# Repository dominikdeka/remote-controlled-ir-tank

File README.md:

# remote-controlled-ir-tank
Arduino based remote controlled vehicle with ir gun

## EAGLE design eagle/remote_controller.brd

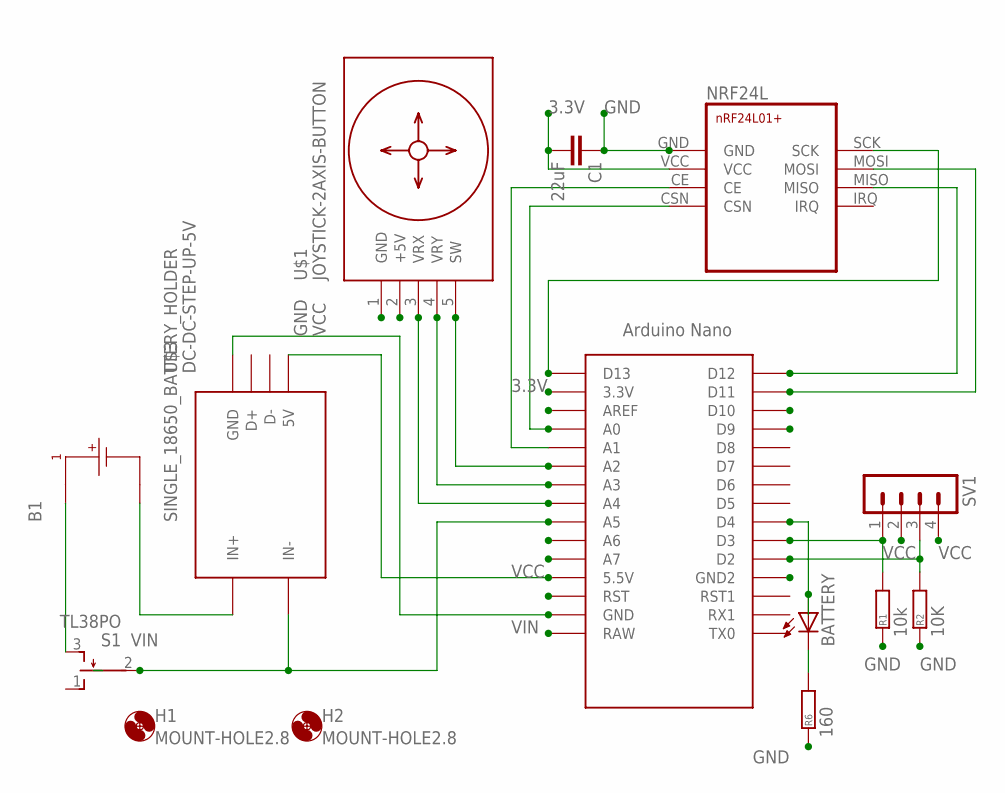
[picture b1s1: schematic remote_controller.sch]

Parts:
B1: SINGLE_18650_BATTERY_HOLDER; SINGLE_18650_HOLDER
BATTERY: LED5MM
C1: 22uF; C025-040X050
H1, H2: MOUNT-HOLE2.8; 2,8
NRF24L: NRF24L01+
R1: 10k; 0204/7
R2: 10K; 0204/7
R6: 160; 0204/7
S1: TL38PO; TL3XPO
SV1: MA04-1
U$1: JOYSTICK-2AXIS-BUTTON
U$2: NANO
U$3: DC-DC-STEP-UP-5V

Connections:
3.3V: C1.2, NRF24L.VCC, U$2.3.3V
A0: NRF24L.CSN, U$2.A0
A1: NRF24L.CE, U$2.A1
A2: U$1.5 (SW), U$2.A2
A3: U$1.4 (VRY), U$2.A3
A4: U$1.3 (VRX), U$2.A4
D2: R2.2, SV1.3, U$2.D2
D3: R1.2, SV1.1, U$2.D3
D4: BATTERY.A, U$2.D4
D9: U$2.D9
D10: U$2.D10
D11: NRF24L.MOSI, U$2.D11
D12: NRF24L.MISO, U$2.D12
D13: NRF24L.SCK, U$2.D13
GND: C1.1, NRF24L.GND, R1.1, R2.1, R6.1, U$1.1 (GND), U$2.GND, U$2.GND1 (GND2), U$3.GND
unnamed: B1.C1_N (1_N), U$3.IN+
unnamed: B1.C1_P (1_P), S1.3 (S)
unnamed: BATTERY.K (C), R6.2
VCC: SV1.2, SV1.4, U$1.2 (+5V), U$2.5V (5.5V), U$3.5V
VIN: S1.2, U$2.A5, U$2.RAW, U$3.IN-

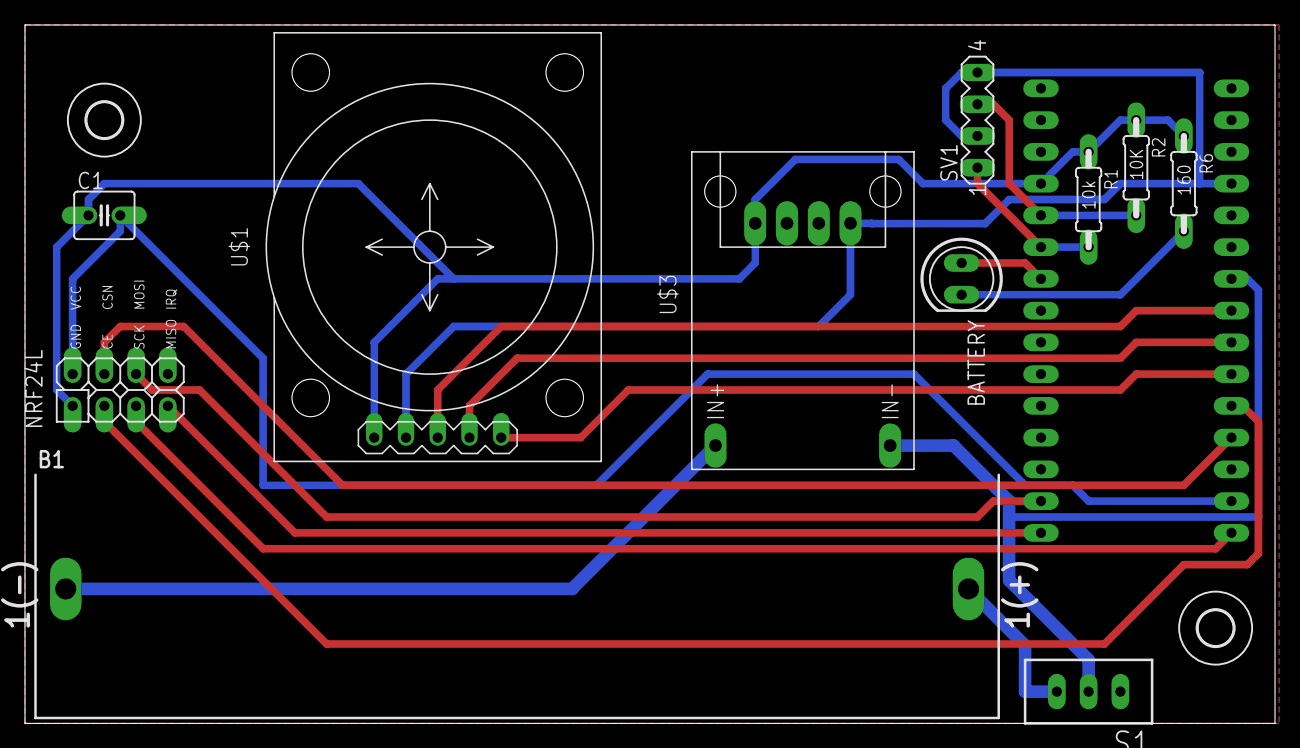
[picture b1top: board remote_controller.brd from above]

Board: 2 copper layers, 100.0 x 55.9 mm, 14 parts (0 on the bottom side), 18 nets.

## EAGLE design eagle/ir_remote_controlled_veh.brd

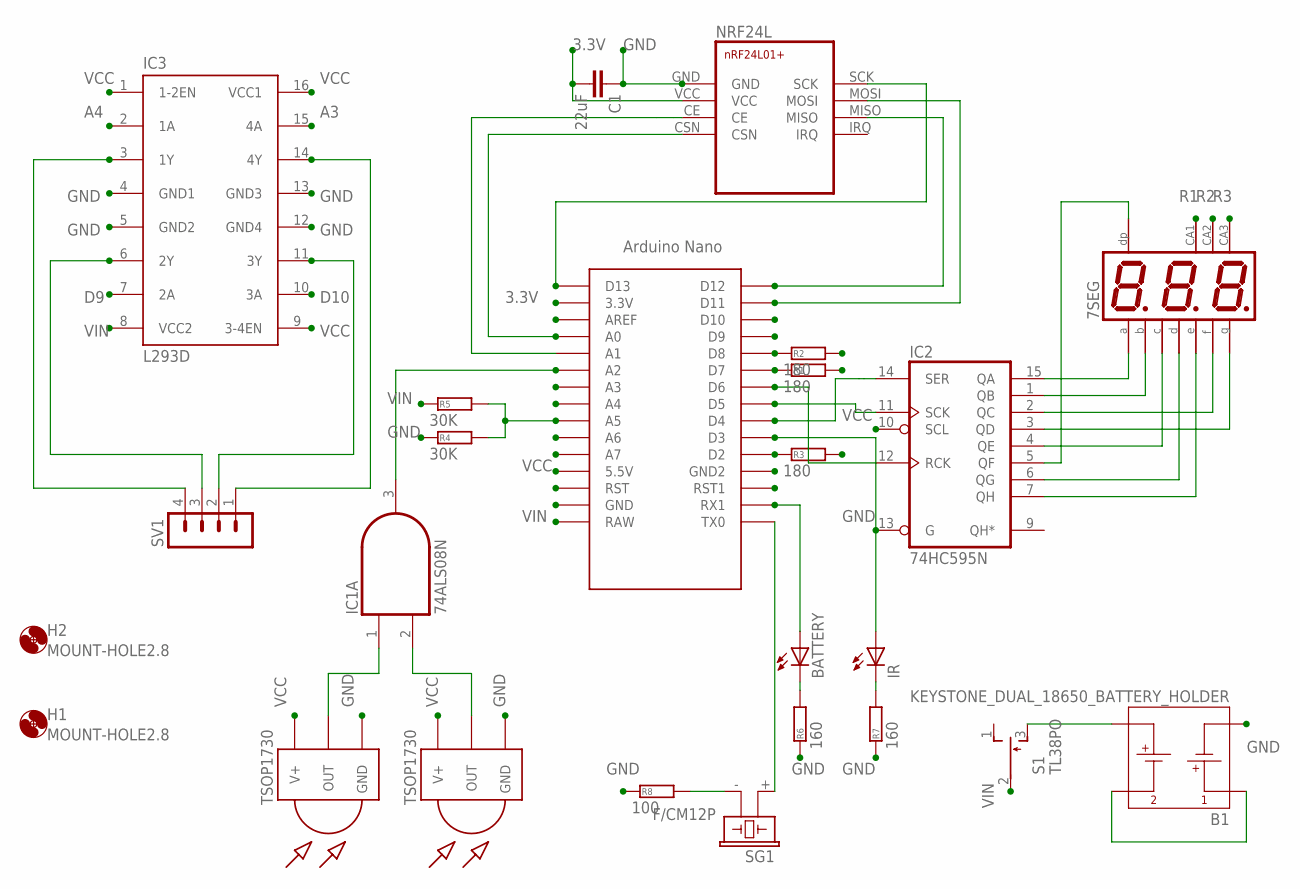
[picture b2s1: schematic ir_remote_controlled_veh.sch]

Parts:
7SEG: BA56-12EWA
B1: KEYSTONE_DUAL_18650_BATTERY_HOLDER; KEYSTONE_1049_DUAL_18650_HOLDER
BATTERY: LED5MM
C1: 22uF; C025-040X050
H1, H2: MOUNT-HOLE2.8; 2,8
IC1: 74ALS08N; DIL14
IC2: 74HC595N; DIL16
IC3: L293D; DIL16
IR: LED5MM
NRF24L: NRF24L01+
R1, R2, R3: 180; 0204/7
R4, R5: 30K; 0204/7
R6, R7: 160; 0204/7
R8: 100; 0204/7
S1: TL38PO; TL3XPO
SG1: F/CM12P
SV1: MA04-1
TSOP1, TSOP2: TSOP1730; TSOP17XX
U$1: NANO

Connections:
3.3V: C1.2, NRF24L.VCC, U$1.3.3V
A0: NRF24L.CSN, U$1.A0
A1: NRF24L.CE, U$1.A1
A2: IC1.3 (O), U$1.A2
A3: IC3.15 (4A), U$1.A3
A4: IC3.2 (1A), U$1.A4
A5: R4.2, R5.2, U$1.A5
D2: R3.1, U$1.D2
D3: IR.A, U$1.D3
D4: IC2.14 (SER), U$1.D4
D5: IC2.11 (SCK), U$1.D5
D6: IC2.12 (RCK), U$1.D6
D7: R1.1, U$1.D7
D8: R2.1, U$1.D8
D9: IC3.7 (2A), U$1.D9
D10: IC3.10 (3A), U$1.D10
D11: NRF24L.MOSI, U$1.D11
D12: NRF24L.MISO, U$1.D12
D13: NRF24L.SCK, U$1.D13
GND: B1.C1_N (1_N), C1.1, IC1.7 (GND), IC2.8 (GND), IC2.13 (G), IC3.4 (GND1), IC3.5 (GND2), IC3.12 (GND4), IC3.13 (GND3), NRF24L.GND, R4.1, R6.1, R7.1, R8.1, TSOP1.GND, TSOP2.GND, U$1.GND, U$1.GND1 (GND2)
unnamed: 7SEG.P$11 (A), IC2.15 (QA)
unnamed: 7SEG.P$7 (B), IC2.1 (QB)
unnamed: 7SEG.P$10 (F), IC2.2 (QC)
unnamed: 7SEG.P$5 (G), IC2.3 (QD)
unnamed: 7SEG.P$4 (C), IC2.4 (QE)
unnamed: 7SEG.P$3 (DP), IC2.5 (QF)
unnamed: 7SEG.P$2 (D), IC2.6 (QG)
unnamed: 7SEG.P$1 (E), IC2.7 (QH)
unnamed: B1.C1_P (1_P), B1.C2_N (2_N)
unnamed: B1.C2_P (2_P), S1.3 (S)
unnamed: SG1.+ (1), U$1.TX0
unnamed: BATTERY.K (C), R6.2
unnamed: IR.K (C), R7.2
unnamed: R8.2, SG1.- (2)
unnamed: IC1.1 (I0), TSOP1.OUT
unnamed: IC1.2 (I1), TSOP2.OUT
unnamed: IC3.6 (2Y), SV1.3
unnamed: IC3.3 (1Y), SV1.4
unnamed: IC3.14 (4Y), SV1.1
unnamed: IC3.11 (3Y), SV1.2
R1: 7SEG.P$8 (CA), R1.2
R2: 7SEG.P$9 (CA), R2.2
R3: 7SEG.P$12 (CA), R3.2
RX1: BATTERY.A, U$1.RX1
VCC: IC1.14 (VCC), IC2.10 (SCL), IC2.16 (VCC), IC3.1 (1-2EN), IC3.9 (3-4EN), IC3.16 (VCC1), TSOP1.V+, TSOP2.V+, U$1.5V (5.5V)
VIN: IC3.8 (VCC2), R5.1, S1.2, U$1.RAW

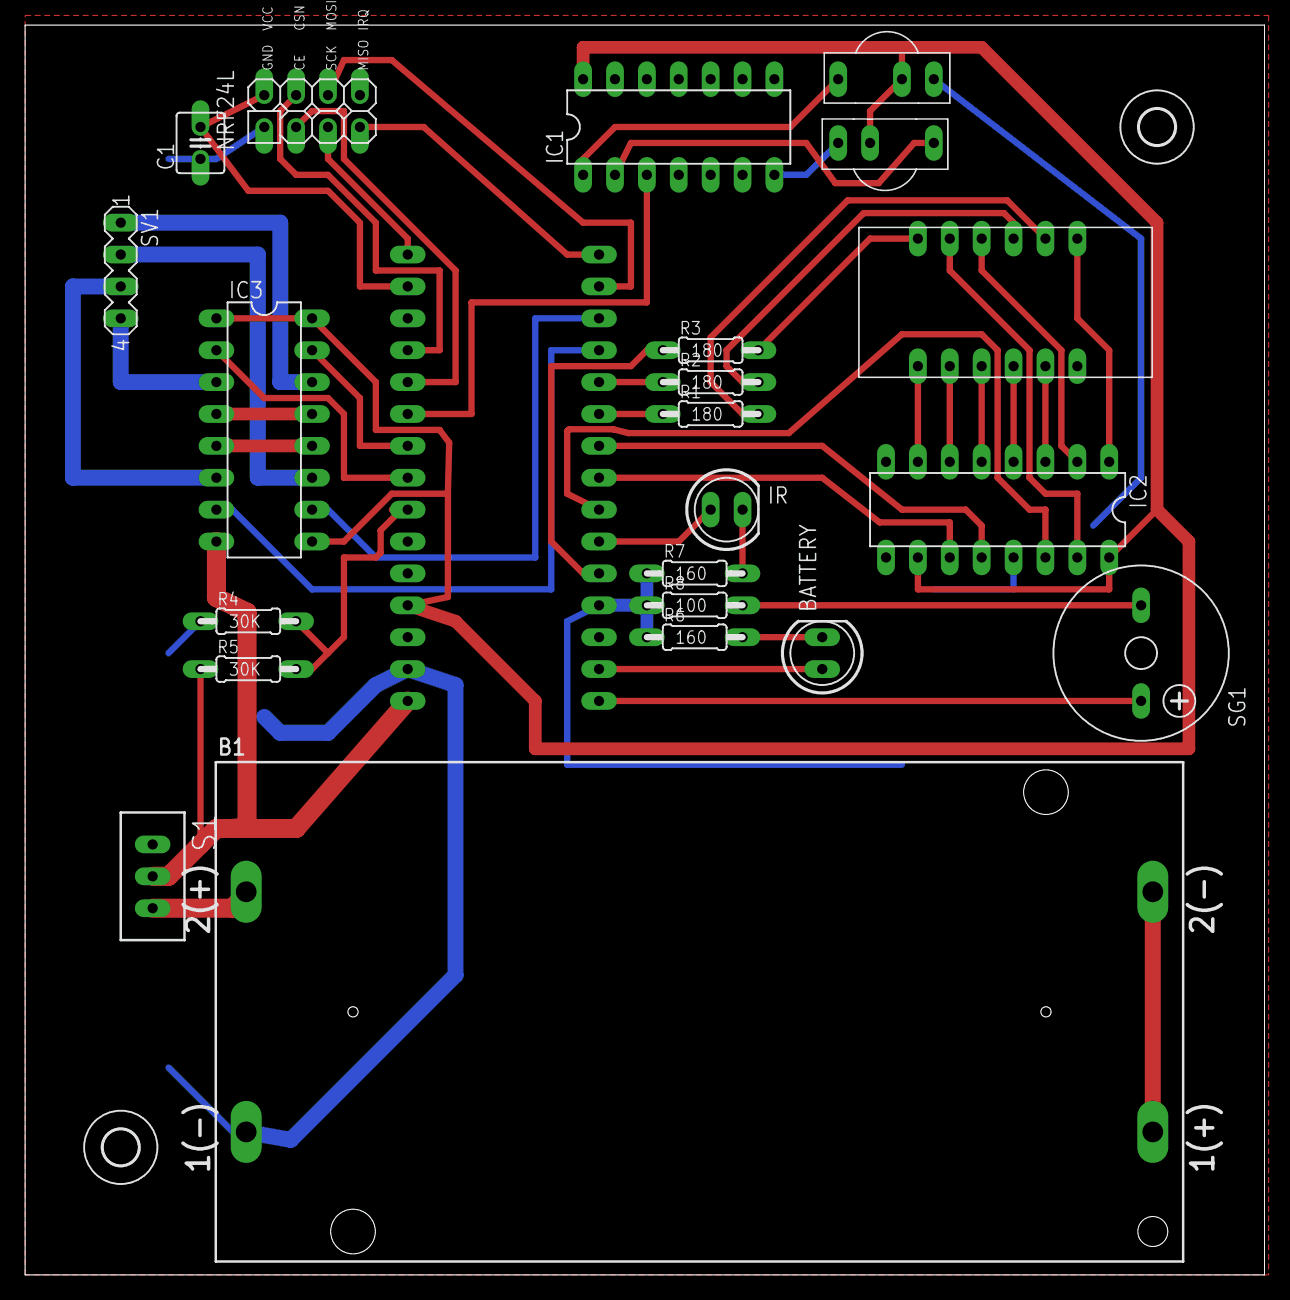
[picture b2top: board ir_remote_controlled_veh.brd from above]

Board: 2 copper layers, 98.7 x 99.6 mm, 25 parts (0 on the bottom side), 46 nets.

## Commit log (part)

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2017-10-18 src added
2017-10-20 refactoring, some reactions added
2017-10-20 refactoring
2020-02-14 new version - initial upload
2020-02-14 eagle files added
